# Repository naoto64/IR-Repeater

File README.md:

# IR-Repeater
Device for relaying infrared remote controls

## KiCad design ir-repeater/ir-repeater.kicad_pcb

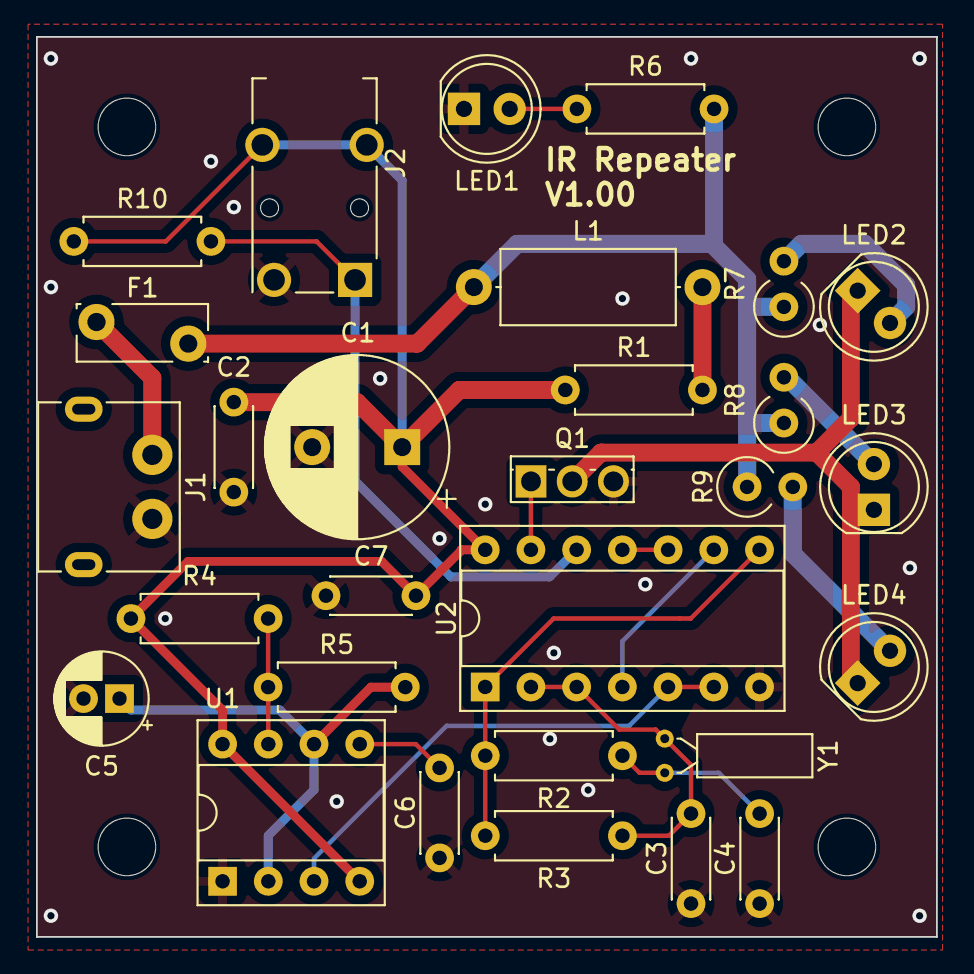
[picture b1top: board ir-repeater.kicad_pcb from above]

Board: 2 copper layers, 50.0 x 50.0 mm, 33 parts (0 on the bottom side), 21 nets.

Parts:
C1: 1000u; CP_Radial_D10.0mm_P5.00mm
C2, C7: 0.1u; C_Disc_D4.3mm_W1.9mm_P5.00mm
C3, C4: 10p; C_Disc_D4.3mm_W1.9mm_P5.00mm
C5: 10u; CP_Radial_D5.0mm_P2.00mm
C6: 0.01u; C_Disc_D4.3mm_W1.9mm_P5.00mm
F1: 0.5A; Fuse_Bourns_MF-RG300
H1, H2, H3, H4: M3; MountingHole_3.2mm_M3
J1: USB_C_Receptacle_PowerOnly_6P; USB_C_PowerOnly
J2: AudioJack3; Jack_3.5mm_Switronic_ST-005-G_horizontal
L1: 1m; L_Axial_L9.5mm_D4.0mm_P12.70mm_Horizontal_Fastron_SMCC
LED1: LED; LED_D5.0mm
LED2, LED3, LED4: LED; LED_D5.0mm_IRGrey
Q1: 2SK4017; TO-251-3_Vertical
R1: 100 1/2W; R_Axial_DIN0207_L6.3mm_D2.5mm_P7.62mm_Horizontal
R2: 470k; R_Axial_DIN0207_L6.3mm_D2.5mm_P7.62mm_Horizontal
R3: 10M; R_Axial_DIN0207_L6.3mm_D2.5mm_P7.62mm_Horizontal
R4: 220k; R_Axial_DIN0207_L6.3mm_D2.5mm_P7.62mm_Horizontal
R5: 1k; R_Axial_DIN0207_L6.3mm_D2.5mm_P7.62mm_Horizontal
R6: 2.2k; R_Axial_DIN0207_L6.3mm_D2.5mm_P7.62mm_Horizontal
R7, R8, R9: 39 1W; R_Axial_DIN0309_L9.0mm_D3.2mm_P2.54mm_Vertical
R10: 10k; R_Axial_DIN0207_L6.3mm_D2.5mm_P7.62mm_Horizontal
U1: NE555P; DIP-8_W7.62mm_Socket
U2: 74HC02; DIP-14_W7.62mm_Socket
Y1: 38kHz; Crystal_DS26_D2.0mm_L6.0mm_Horizontal

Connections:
+5V: C1.1, C2.1, C7.2, J2.T, R1.1, R4.1, R10.1, U1.4 (R), U1.8 (VCC), U2.14 (VCC)
GND: C1.2, C2.2, C3.1, C4.1, C5.2, C6.1, C7.1, J1.A12 (GND), J2.S, LED1.1 (K), Q1.3 (S), U1.1 (GND), U2.7 (GND)
unnamed: C3.2, R3.1, U2.2, U2.3, Y1.2
unnamed: C4.2, R2.1, Y1.1
unnamed: F1.1, J1.A9 (VBUS)
unnamed: J2.R, R10.2, U2.12
unnamed: L1.2, R1.2
unnamed: LED1.2 (A), R6.1
unnamed: LED2.2 (A), R7.2
unnamed: LED2.1 (K), LED3.1 (K), LED4.1 (K), Q1.2 (D)
unnamed: LED3.2 (A), R8.2
unnamed: LED4.2 (A), R9.2
unnamed: Q1.1 (G), U2.13
unnamed: R2.2, R3.2, U2.1, U2.8
unnamed: C6.2, U1.5 (CV)
unnamed: R4.2, R5.1, U1.7 (DIS)
unnamed: U1.3 (Q), U2.5, U2.6
unnamed: C5.1, R5.2, U1.2 (TR), U1.6 (THR)
unnamed: U2.4, U2.9
unnamed: U2.10, U2.11
VBUS: F1.2, L1.1, R6.2, R7.1, R8.1, R9.1

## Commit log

2025-03-01 Rename docs/implementation-diagram.jpg to docs/img/implementation-diagram.jpg
2025-03-01 Rename docs/implementation-example.jpg to docs/img/implementation-example.jpg
2025-03-01 Rename docs/schematic.jpg to docs/img/schematic.jpg
